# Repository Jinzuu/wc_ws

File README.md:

wc_ws
=====

Wordclock on STM32 with WS LEDs

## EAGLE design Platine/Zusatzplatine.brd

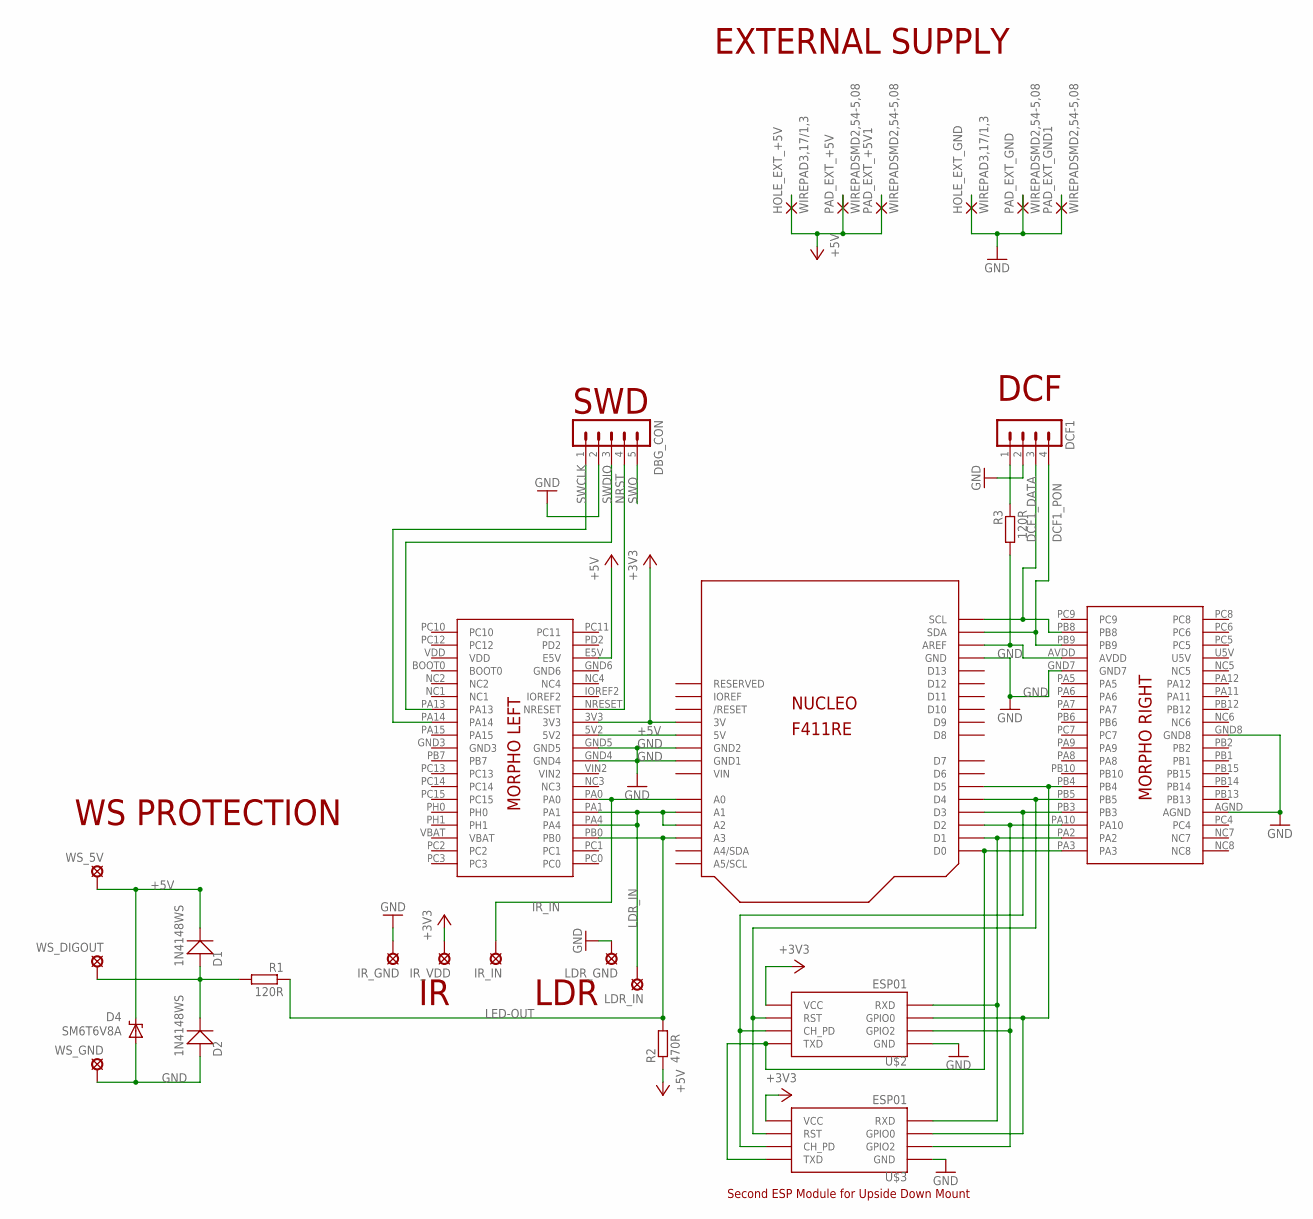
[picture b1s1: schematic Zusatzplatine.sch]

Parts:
D1, D2: 1N4148WS; SOD-323
D4: SM6T6V8A; SMBJ
DBG_CON: MA05-1
DCF1: MA04-1
HOLE_EXT_+5V: WIREPAD3,17/1,3; 3,17/1,3
HOLE_EXT_GND: WIREPAD3,17/1,3; 3,17/1,3
IR_GND: SE14
IR_IN: SE14
IR_VDD: SE14
LDR_GND: SE14
LDR_IN: SE14
PAD_EXT_+5V, PAD_EXT_+5V1: WIREPADSMD2,54-5,08; SMD2,54-5,08
PAD_EXT_GND, PAD_EXT_GND1: WIREPADSMD2,54-5,08; SMD2,54-5,08
R1, R3: 120R; R1206
R2: 470R; R1206
U$1: NUCLEO_F411RE; NUCLEO_BRD64
U$2, U$3: ESP01
WS_5V: SE14
WS_DIGOUT: SE14
WS_GND: SE14

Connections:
+3V3: IR_VDD.MP, U$1.3V, U$1.3V3, U$2.VCC, U$3.VCC
+5V: D1.1, D4.C, HOLE_EXT_+5V.1, PAD_EXT_+5V.1, PAD_EXT_+5V1.1, R2.1, U$1.5V, U$1.5V2, U$1.E5V, WS_5V.MP
DCF1_DATA: DCF1.3, U$1.PB8, U$1.SCL
DCF1_PON: DCF1.4, U$1.PB9, U$1.SDA
GND: D2.0, D4.A, DBG_CON.2, DCF1.2, HOLE_EXT_GND.1, IR_GND.MP, LDR_GND.MP, PAD_EXT_GND.1, PAD_EXT_GND1.1, U$1.AGND, U$1.GND, U$1.GND1, U$1.GND2, U$1.GND4, U$1.GND5, U$1.GND7, U$1.GND8, U$2.GND, U$3.GND, WS_GND.MP
GND3: U$1.GND3
GND6: U$1.GND6
IR_IN: IR_IN.MP, U$1.A0, U$1.PA0
LDR_IN: LDR_IN.MP, U$1.A1, U$1.A2, U$1.PA1, U$1.PA4
LED-OUT: R1.1, R2.2, U$1.A3, U$1.PB0
unnamed: R3.2, U$1.AREF, U$1.AVDD
unnamed: DCF1.1, R3.1
unnamed: D1.0, D2.1, R1.2, WS_DIGOUT.MP
unnamed: U$1.D5, U$1.PB4, U$2.GPIO0, U$3.GPIO0
unnamed: U$1.D4, U$1.PB5, U$2.RST, U$3.RST
unnamed: U$1.D3, U$1.PB3, U$2.CH_PD, U$3.CH_PD
unnamed: U$1.D0, U$1.PA3, U$2.TX (TXD), U$3.TX (TXD)
unnamed: U$1.D1, U$1.PA2, U$2.RX (RXD), U$3.RX (RXD)
unnamed: U$1.D2, U$1.PA10, U$2.GPIO2, U$3.GPIO2
NRST: DBG_CON.4, U$1.NRESET
SWCLK: DBG_CON.1, U$1.PA14
SWDIO: DBG_CON.3, U$1.PA13
SWO: DBG_CON.5
U5V: U$1.U5V
VBAT: U$1.VBAT
VDD: U$1.VDD
VIN: U$1.VIN
VIN2: U$1.VIN2

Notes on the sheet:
DCF
EXTERNAL SUPPLY
WS PROTECTION
LDR
SWD
Second ESP Module for Upside Down Mount

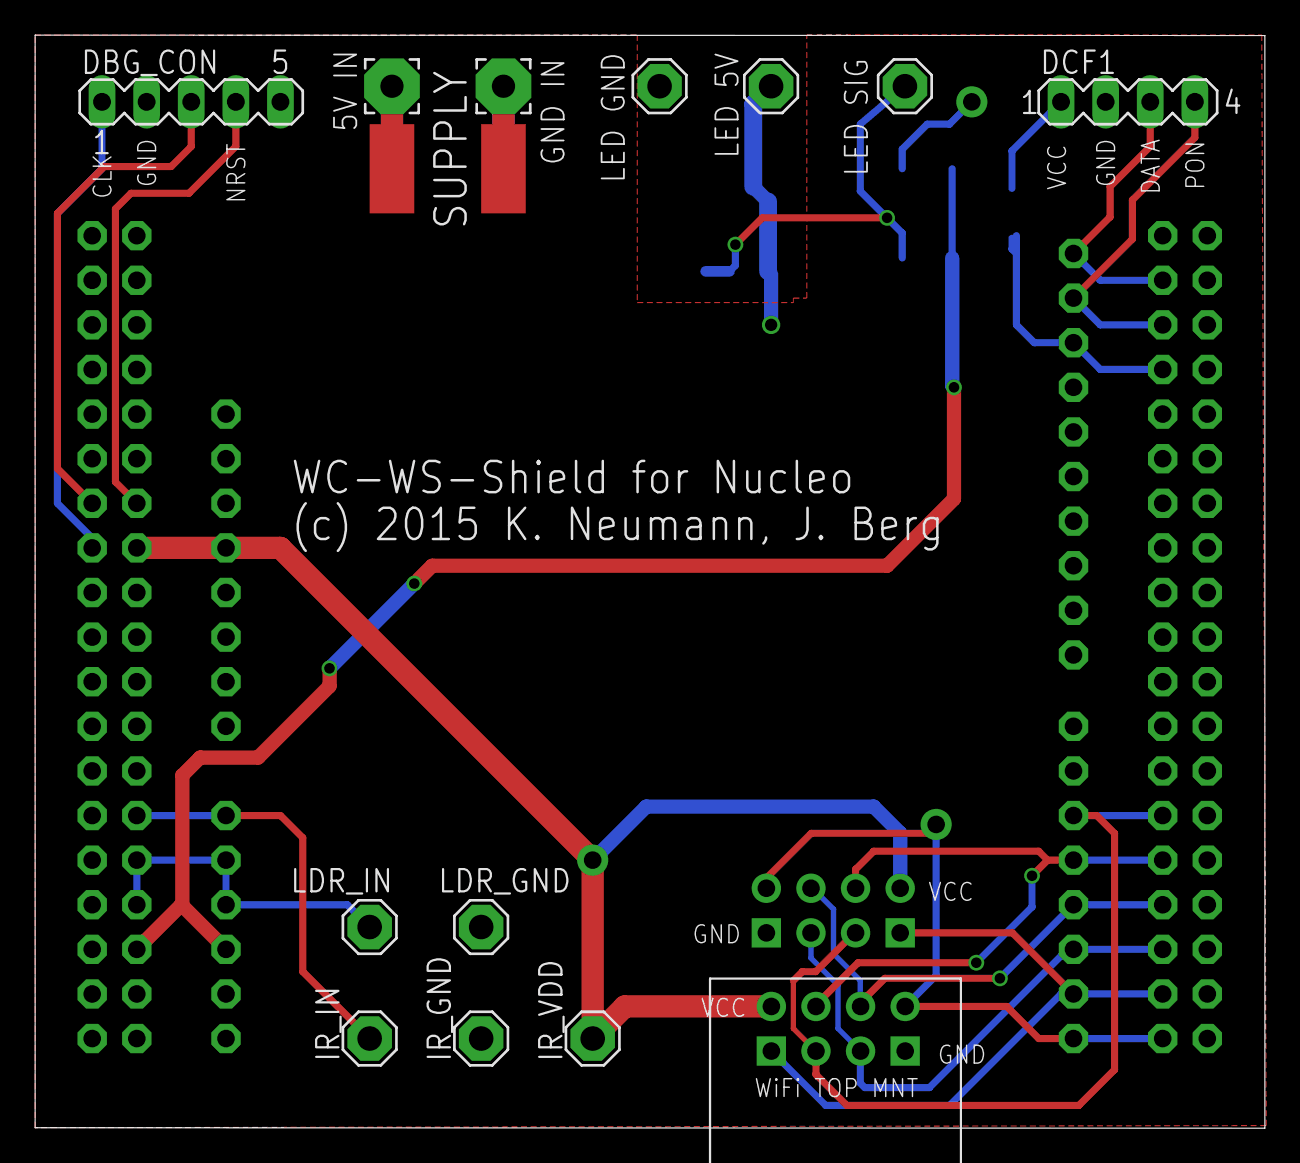
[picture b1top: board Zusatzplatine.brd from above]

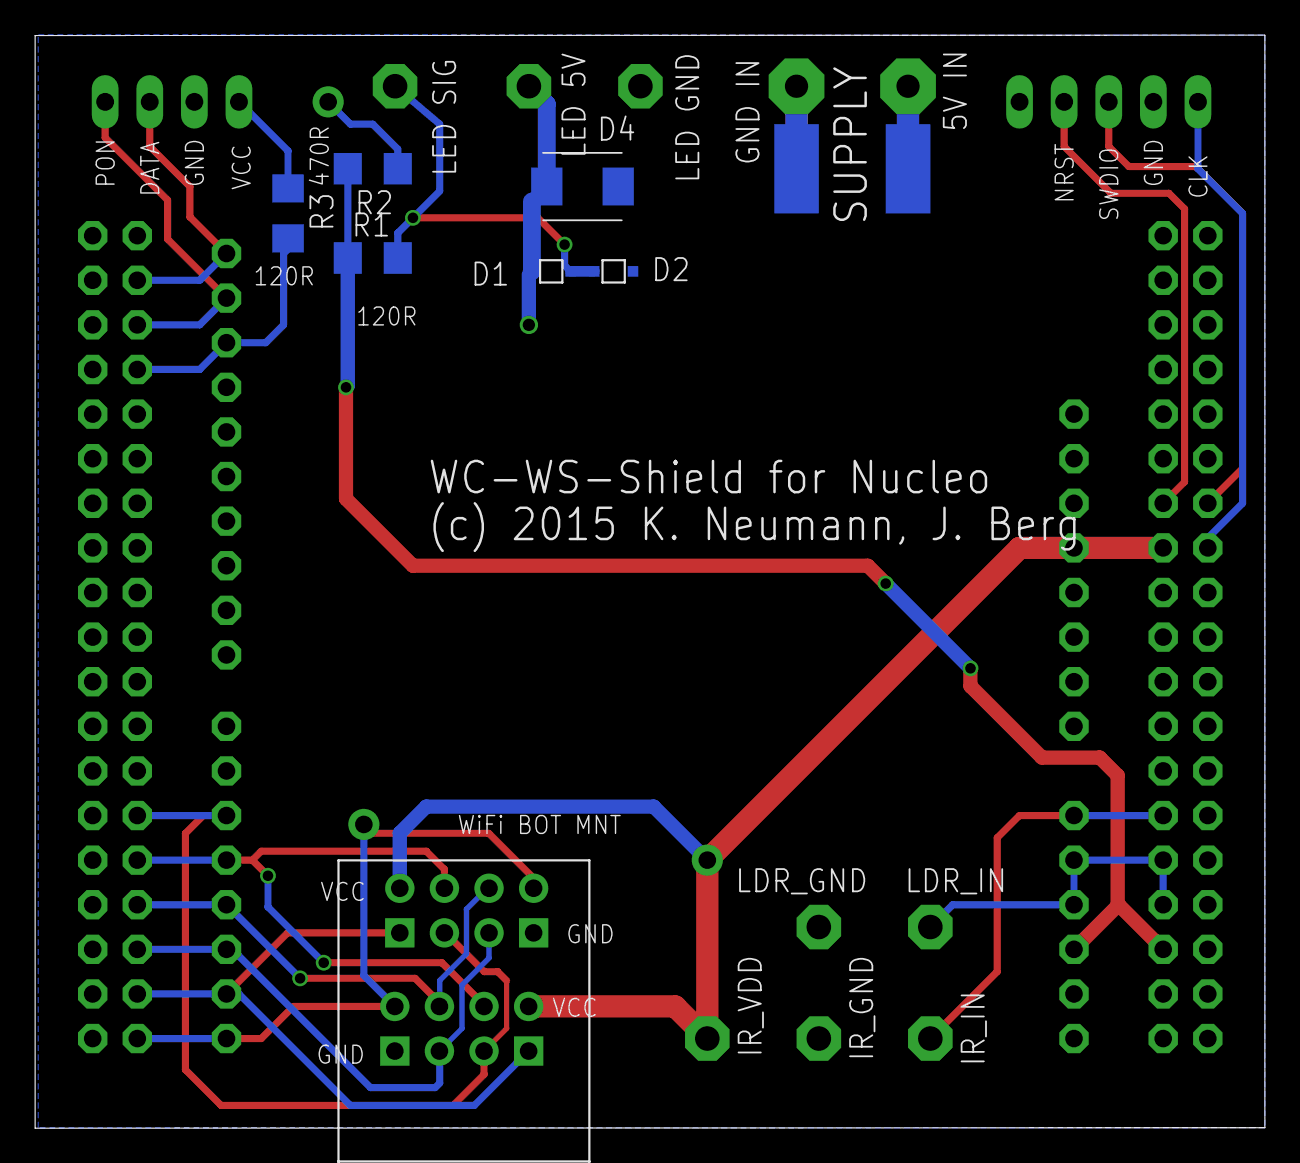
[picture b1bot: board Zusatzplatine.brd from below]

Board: 2 copper layers, 70.0 x 62.2 mm, 25 parts (9 on the bottom side), 20 nets.

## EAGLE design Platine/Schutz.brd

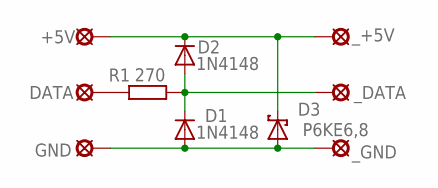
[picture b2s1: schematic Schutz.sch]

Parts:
+5V: LSP11
D1, D2: 1N4148; DO35-7
D3: P6KE6,8; CB417-15
DATA: LSP11
GND: LSP11
R1: 270; 0207/7
_+5V: LSP11
_DATA: LSP11
_GND: LSP11

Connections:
unnamed: D1.C, D2.A, R1.2, _DATA.MP
unnamed: D1.A, D3.A, GND.MP, _GND.MP
unnamed: +5V.MP, D2.C, D3.C, _+5V.MP
unnamed: DATA.MP, R1.1

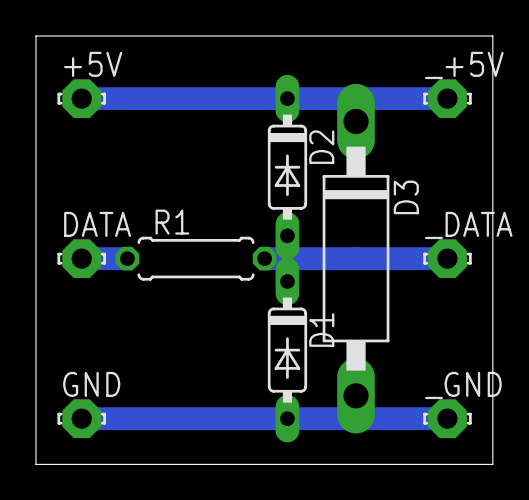
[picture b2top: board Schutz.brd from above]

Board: 2 copper layers, 25.4 x 23.8 mm, 10 parts (0 on the bottom side), 4 nets.

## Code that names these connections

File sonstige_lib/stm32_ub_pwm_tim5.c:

//--------------------------------------------------------------
// File     : stm32_ub_pwm_tim5.c
// Datum    : 26.03.2013
// Version  : 1.0
// Autor    : UB
// EMail    : mc-4u(@)t-online.de
// Web      : www.mikrocontroller-4u.de
// CPU      : STM32F4
// IDE      : CooCox CoIDE 1.7.0
// Module   : GPIO, TIM
// Funktion : PWM-Funktionen per Timer5
//
// Hinweis  : mögliche Pinbelegungen
//            CH1 : [PA0]
//            CH2 : [PA1]
//            CH3 : [PA2]
//            CH4 : [PA3]
//--------------------------------------------------------------


//--------------------------------------------------------------
// Includes
//--------------------------------------------------------------
#include "stm32_ub_pwm_tim5.h"



//--------------------------------------------------------------
// interne Funktionen
//--------------------------------------------------------------
void P_PWM_InitIO_TIM5(void);
void P_PWM_InitTIM5(void);


//--------------------------------------------------------------
// Definition aller PWM Pins
// Reihenfolge wie bei PWM_TIM5_NAME_t
//
// Channel : [1...4]
// Init = Startwert : [0...PWM_TIM5_PERIODE]
//--------------------------------------------------------------
PWM_TIM5_t PWM_TIM5[] = {
  // Name     ,Channel, PORT , PIN       , CLOCK               , Source         , Init
  {PWM_T5_PA2 ,3      ,GPIOA ,GPIO_Pin_2 ,RCC_AHB1Periph_GPIOA ,GPIO_PinSource2 ,  64},
};



//--------------------------------------------------------------
// init und start vom PWM mit Timer5
//-------------------------------------------------------------- 
void UB_PWM_TIM5_Init(void)
{
  P_PWM_InitIO_TIM5();
  P_PWM_InitTIM5();
}


//--------------------------------------------------------------
// stellt einen PWM-Wert für einen Kanal ein 
// wert : [0 bis PWM_TIM5_PERIODE]
//--------------------------------------------------------------
void UB_PWM_TIM5_SetPWM(PWM_TIM5_NAME_t pwm, uint16_t wert)
{
  if(wert>PWM_TIM5_PERIODE) wert=PWM_TIM5_PERIODE;

  if(PWM_TIM5[pwm].CHANNEL==1) {
    TIM5->CCR1 = wert;
  } 
  if(PWM_TIM5[pwm].CHANNEL==2) {
    TIM5->CCR2 = wert;
  } 
  if(PWM_TIM5[pwm].CHANNEL==3) {
    TIM5->CCR3 = wert;
  } 
  if(PWM_TIM5[pwm].CHANNEL==4) {
    TIM5->CCR4 = wert;
  } 
}


//--------------------------------------------------------------
// interne Funktion
// Init aller IO-Pins
//--------------------------------------------------------------
void P_PWM_InitIO_TIM5(void)
{
  GPIO_InitTypeDef GPIO_InitStructure;
  PWM_TIM5_NAME_t pwm_name;

  for(pwm_name=0;pwm_name<PWM_TIM5_ANZ;pwm_name++) {
    // Clock Enable
    RCC_AHB1PeriphClockCmd(PWM_TIM5[pwm_name].PWM_CLK, ENABLE);

    // Config des Pins als Digital-Ausgang
    GPIO_InitStructure.GPIO_Pin = PWM_TIM5[pwm_name].PWM_PIN;
    GPIO_InitStructure.GPIO_Mode = GPIO_Mode_AF;
    GPIO_InitStructure.GPIO_Speed = GPIO_Speed_100MHz;
    GPIO_InitStructure.GPIO_OType = GPIO_OType_PP;
    GPIO_InitStructure.GPIO_PuPd = GPIO_PuPd_UP ;
    GPIO_Init(PWM_TIM5[pwm_name].PWM_PORT, &GPIO_InitStructure);

    // Alternative-Funktion mit dem IO-Pin verbinden
    GPIO_PinAFConfig(PWM_TIM5[pwm_name].PWM_PORT, PWM_TIM5[pwm_name].PWM_SOURCE, GPIO_AF_TIM5);
  }  
}


//--------------------------------------------------------------
// interne Funktion
// Init vom Timer
//--------------------------------------------------------------
void P_PWM_InitTIM5(void)
{
  TIM_TimeBaseInitTypeDef  TIM_TimeBaseStructure;
  TIM_OCInitTypeDef  TIM_OCInitStructure;
  PWM_TIM5_NAME_t pwm_name;
  uint16_t wert;

  // Clock enable
  RCC_APB1PeriphClockCmd(RCC_APB1Periph_TIM5, ENABLE); 

  // Timer init
  TIM_TimeBaseStructure.TIM_Period = PWM_TIM5_PERIODE;
  TIM_TimeBaseStructure.TIM_Prescaler = PWM_TIM5_PRESCALE;
  TIM_TimeBaseStructure.TIM_ClockDivision = TIM_CKD_DIV1;
  TIM_TimeBaseStructure.TIM_CounterMode = TIM_CounterMode_Up;
  TIM_TimeBaseInit(TIM5, &TIM_TimeBaseStructure);


  for(pwm_name=0;pwm_name<PWM_TIM5_ANZ;pwm_name++) {
    if(PWM_TIM5[pwm_name].CHANNEL==1) {
      // Channel 1
      TIM_OCInitStructure.TIM_OCMode = TIM_OCMode_PWM1;
      TIM_OCInitStructure.TIM_OutputState = TIM_OutputState_Enable;
      wert=PWM_TIM5[pwm_name].PWM_INIT;
      if(wert>PWM_TIM5_PERIODE) wert=PWM_TIM5_PERIODE;
      TIM_OCInitStructure.TIM_Pulse = wert;
      TIM_OCInitStructure.TIM_OCPolarity = PWM_TIM5_POLARITY;
      TIM_OC1Init(TIM5, &TIM_OCInitStructure);
      TIM_OC1PreloadConfig(TIM5, TIM_OCPreload_Enable);
    }
    if(PWM_TIM5[pwm_name].CHANNEL==2) {
      // Channel 2
      TIM_OCInitStructure.TIM_OCMode = TIM_OCMode_PWM1;
      TIM_OCInitStructure.TIM_OutputState = TIM_OutputState_Enable;
      wert=PWM_TIM5[pwm_name].PWM_INIT;
      if(wert>PWM_TIM5_PERIODE) wert=PWM_TIM5_PERIODE;
      TIM_OCInitStructure.TIM_Pulse = wert;
      TIM_OCInitStructure.TIM_OCPolarity = PWM_TIM5_POLARITY;
      TIM_OC2Init(TIM5, &TIM_OCInitStructure);
      TIM_OC2PreloadConfig(TIM5, TIM_OCPreload_Enable);
    }
    if(PWM_TIM5[pwm_name].CHANNEL==3) {
      // Channel 3
      TIM_OCInitStructure.TIM_OCMode = TIM_OCMode_PWM1;
      TIM_OCInitStructure.TIM_OutputState = TIM_OutputState_Enable;
      wert=PWM_TIM5[pwm_name].PWM_INIT;
      if(wert>PWM_TIM5_PERIODE) wert=PWM_TIM5_PERIODE;
      TIM_OCInitStructure.TIM_Pulse = wert;
      TIM_OCInitStructure.TIM_OCPolarity = PWM_TIM5_POLARITY;
      TIM_OC3Init(TIM5, &TIM_OCInitStructure);
      TIM_OC3PreloadConfig(TIM5, TIM_OCPreload_Enable);
    }
    if(PWM_TIM5[pwm_name].CHANNEL==4) {
      // Channel 4
      TIM_OCInitStructure.TIM_OCMode = TIM_OCMode_PWM1;
      TIM_OCInitStructure.TIM_OutputState = TIM_OutputState_Enable;
      wert=PWM_TIM5[pwm_name].PWM_INIT;
      if(wert>PWM_TIM5_PERIODE) wert=PWM_TIM5_PERIODE;
      TIM_OCInitStructure.TIM_Pulse = wert;
      TIM_OCInitStructure.TIM_OCPolarity = PWM_TIM5_POLARITY;
      TIM_OC4Init(TIM5, &TIM_OCInitStructure);
      TIM_OC4PreloadConfig(TIM5, TIM_OCPreload_Enable);
    }
  }

  // Timer enable
  TIM_ARRPreloadConfig(TIM5, ENABLE);
  TIM_Cmd(TIM5, ENABLE);
}

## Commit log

2014-02-17 - initial commit
2014-02-17 - changed project name
2014-02-22 Updated UB Timer Libs
2014-02-22 Fixed error due to update in timer library
2014-10-10 - integrated ub_ws lib - not tested, but compiling
2014-10-11 DCF77 code now working
2014-10-11 - handling of segments "ES" and "IST" changed
2014-10-11 - Added function to switch all elements off
2014-10-12 Code added to translate RTC time to active LEDs
2014-10-12 Added IR remote functionality with IRMP (note: IR reception is untested)
2014-10-12 added forgotten files
2014-10-13 Added brightness multiplier array
2014-10-20 Added colors
2014-10-27 Made code compatible with pre c99 mode and removed compiler flag. Works :)
2014-10-30 Added colors for remote
2014-11-02 Configured for NUCLEO 411re board (Clock 96 MHz)
    Removed compilation errors
2014-11-02 LDR Sampling added and tested Tested IR reception
2014-11-09 DCF77 tested again on new pins Renamed commonMath.cpp to .c
2014-11-10 - included docs
2014-11-10 - included RTC - ISR routine in main.c working
2014-11-11 Word matrix depending is set depending on RTC OneMinuteISR RTC is updated by DCF reception Top left LED now indicates DCF reception state (green ok, red bad signal)
2014-11-17 Adapted keys IDs to new version of ED618 IR remote from DX
2014-12-10 Reworked light dependent brightness code Integrated IR settability of brightness based on ambient brightness
2014-12-10 Recalculated WS2812 timings to Nucleo Clocks
    Updated documentation
2014-12-10 Fixed small bug in WC Frontend
2014-12-11 Updated wc_frontend to actual word matrix used
2014-12-11 Changed minute dots for easier cabling
2014-12-11 After testing, minor changes/bugfixes
2014-12-12 Added code that triggers a waiting for DCF time if last DCF rx is too old
2014-12-22 - mechanische Zeichnungen
2014-12-29 Fixed bug in front end that caused disabled LEDs to be still active Fixed bug in conversion from time to LED matrix Added simple test mode (only addable by defines in main.h)
2014-12-29 Fixed bug due to overlapping word config defines
2015-01-10 - Dokumentation begonnen
2015-02-14 - Rechtschreibung Doku
2015-02-21 - changed output PIN for WS-LEDs to PB0
2015-03-21 - Pin-belegung in Dokumentation eingepflegt
2015-03-28 Documentation Bugfix in main.h
2015-04-07 - bugfix (einS - Stunde curly brackets were missing) - thanks to Mana!
2015-05-21 - updated docu with WLAN pins - included PCB
2015-05-21 - updated docu
2015-06-02 - Platine erweitert
2015-06-03 - Platine weiter
2015-06-03 - Lib gemacht
2015-06-03 - kleine Änderungen - Beschriftungen
2015-06-04 - Platine Fehler behoben
2015-10-25 - Platine überarbeitet
2015-10-26 - Platine auf Arduino Connectors umgestellt
2015-10-26 - added SW4STM32 project
2015-10-27 Corrected layout of top right pin row for arduino interfacing
2015-10-28 Added Library for Stm32F411RE Nucleo Board
2015-10-29 Corrected Nucleo Library
2015-10-29 Reworked Board Design
2015-10-29 Platine: * WS-Schutz Layout verbessert * +5V & GND Leiterbahnen gelöscht (da wir Polygons haben) * DCF-In & DCF-PON auf Arduino Connector verlegt * kleine Trace-Umlegungen um Leitfähigkeit der Polygo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
    Dokumentation aktualisiert
2015-10-30 Increased Drill for esp8266 module pins
2015-10-30 Added Upside Down Mount Option for WiFI Improved Documentation on Board
2015-10-30 - DCF-Leitungen umgelegt - Doku korrigiert
2015-10-30 - Parallele Verbindung zu Morpho-Connectors
2015-10-30 Silkscreen optimized
2015-11-07 - small error fix concerning includes
2015-11-14 - neue Platine in Betrieb genommen
2015-11-14 - included ub_uart_lib - included esp8266 lib
2015-11-14 - UART am Laufen - Kommunikation mit ESP läuft aber noch nicht
2015-11-26 - Bauteilliste begonnen
2016-05-01 !!!! DCF disabled: see main.h for #define DISABLE_DCF - ESP8266 included - ESP8266 gets time from Google.com-Header
2016-05-01 - added ESP8266 Flash Tool
2018-10-08 !!! not a building/working commit !!! - added missing files
2018-10-09 Added CoIDE Project file
2018-10-15 - created TrueStudio Project - now compiling - corrected PinConfiguration for Nucleo Board
2018-10-15 - fixed ESP WLAN chip - now working with WiFi
2018-10-15 - Update der Dokumentation
2018-11-04 - Corrected winter time handling
2020-01-28 - Updated Doku
2020-01-28 - Added ESP32 section to Documentation

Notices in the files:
Platine/Zusatzplatine.brd:
(c) 2015 K. Neumann, J. Berg
